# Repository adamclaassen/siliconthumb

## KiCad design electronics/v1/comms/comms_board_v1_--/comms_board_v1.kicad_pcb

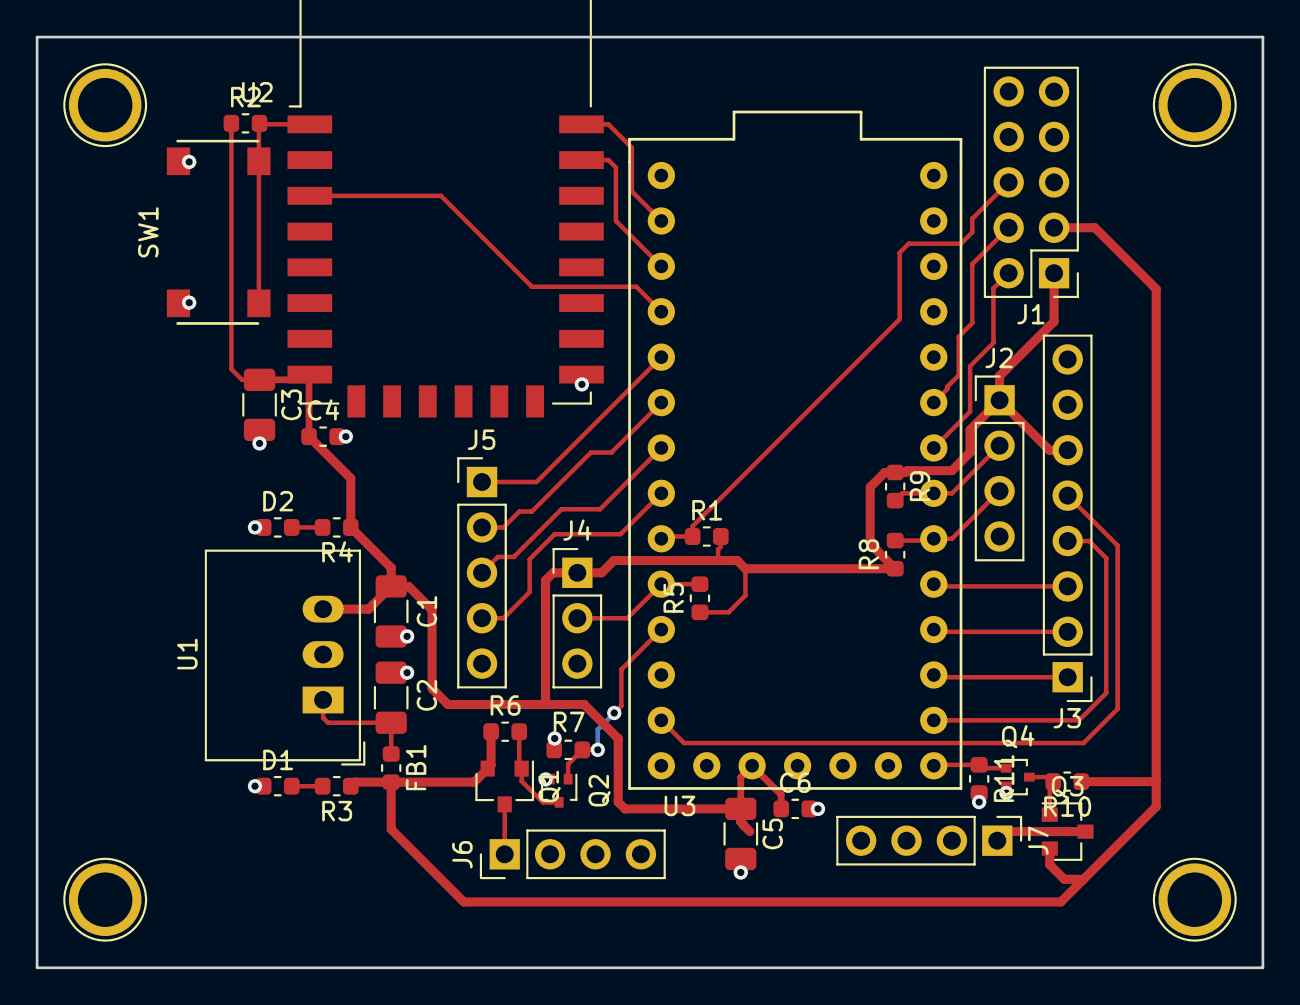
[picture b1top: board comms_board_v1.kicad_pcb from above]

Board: 2 copper layers, 68.6 x 52.1 mm, 35 parts (0 on the bottom side), 31 nets.

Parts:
C1, C2, C3, C5: 10uF; R_1206_3216Metric
C4, C6: 100nF; R_0603_1608Metric
D1, D2: LED; R_0603_1608Metric
FB1: Ferrite_Bead; R_0603_1608Metric
J1: Conn_02x05_Odd_Even; PinHeader_2x05_P2.54mm_Vertical
J2, J6, J7: Conn_01x04; PinHeader_1x04_P2.54mm_Vertical
J3: Conn_01x08; PinHeader_1x08_P2.54mm_Vertical
J4: Conn_01x03; PinHeader_1x03_P2.54mm_Vertical
J5: Conn_01x05; PinHeader_1x05_P2.54mm_Vertical
Q1, Q3: Q_PMOS_GSD; SOT-23
Q2, Q4: Q_NMOS_GSD; SOT-416
R1, R5: 4.7k; R_0603_1608Metric
R2: 100k; R_0603_1608Metric
R3: 22k; R_0603_1608Metric
R4: 2.2k; R_0603_1608Metric
R6, R7, R8, R9, R10, R11: 10k; R_0603_1608Metric
SW1: SW_Push; CnK_PTS645_SMD
U1: R-78E3.3-1.0; Converter_DCDC_RECOM_R-78E-0.5_THT
U2: ESP-12E
U3: TEENSY32; Teensy32

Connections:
+3.3V_MCU: C1.1, C3.1, C4.1, C5.1, C6.1, J1.1, J2.1, J3.6, J4.1, R1.2, R2.1, R4.1, R5.1, R8.1, R9.1, U1.3, U2.8, U3.32
+12V: FB1.2, J1.3, Q1.2, Q3.2, R3.1, R6.1, R10.1
/1WIRE_LED: J1.6, R1.1, U3.9
/1WIRE_SOIL: J4.2, R5.2, U3.10
/CS: J3.1, U3.17
/DISP_DC: J3.3, U3.19
/DISP_RST: J3.2, U3.18
/ESP_EN: U2.3, U3.4
/ESP_RX: U2.21, U3.3
/ESP_TX: U2.22, U3.2
/FAN: Q2.1, R7.1, U3.11
/IR_CTRL: J1.2, U3.22
/MOSI: J3.5, U3.13
/PUMP: Q4.1, R11.1, U3.15
/SCK: J3.4, U3.16
/SCL: J2.2, R9.2, U3.21
/SDA: J2.3, R8.2, U3.20
/UV_CTRL: J1.4, U3.23
GND: C1.2, C2.2, C3.2, C4.2, C5.2, C6.2, D1.1, D2.1, J1.5, J1.7, J1.8, J1.9, J1.10, J2.4, J3.8, J4.3, J5.5, J6.4, J7.4, Q2.2, Q4.2, R7.2, R11.2, SW1.1, U1.2, U2.15, U3.1, U3.27
unnamed: C2.1, FB1.1, U1.1
unnamed: D1.2, R3.2
unnamed: D2.2, R4.2
unnamed: J5.1, U3.5
unnamed: J5.2, U3.6
unnamed: J5.3, U3.7
unnamed: J5.4, U3.8
unnamed: J6.1, Q1.3
unnamed: J7.1, Q3.3
unnamed: Q1.1, Q2.3, R6.2
unnamed: Q3.1, Q4.3, R10.2
unnamed: R2.2, SW1.2, U2.1

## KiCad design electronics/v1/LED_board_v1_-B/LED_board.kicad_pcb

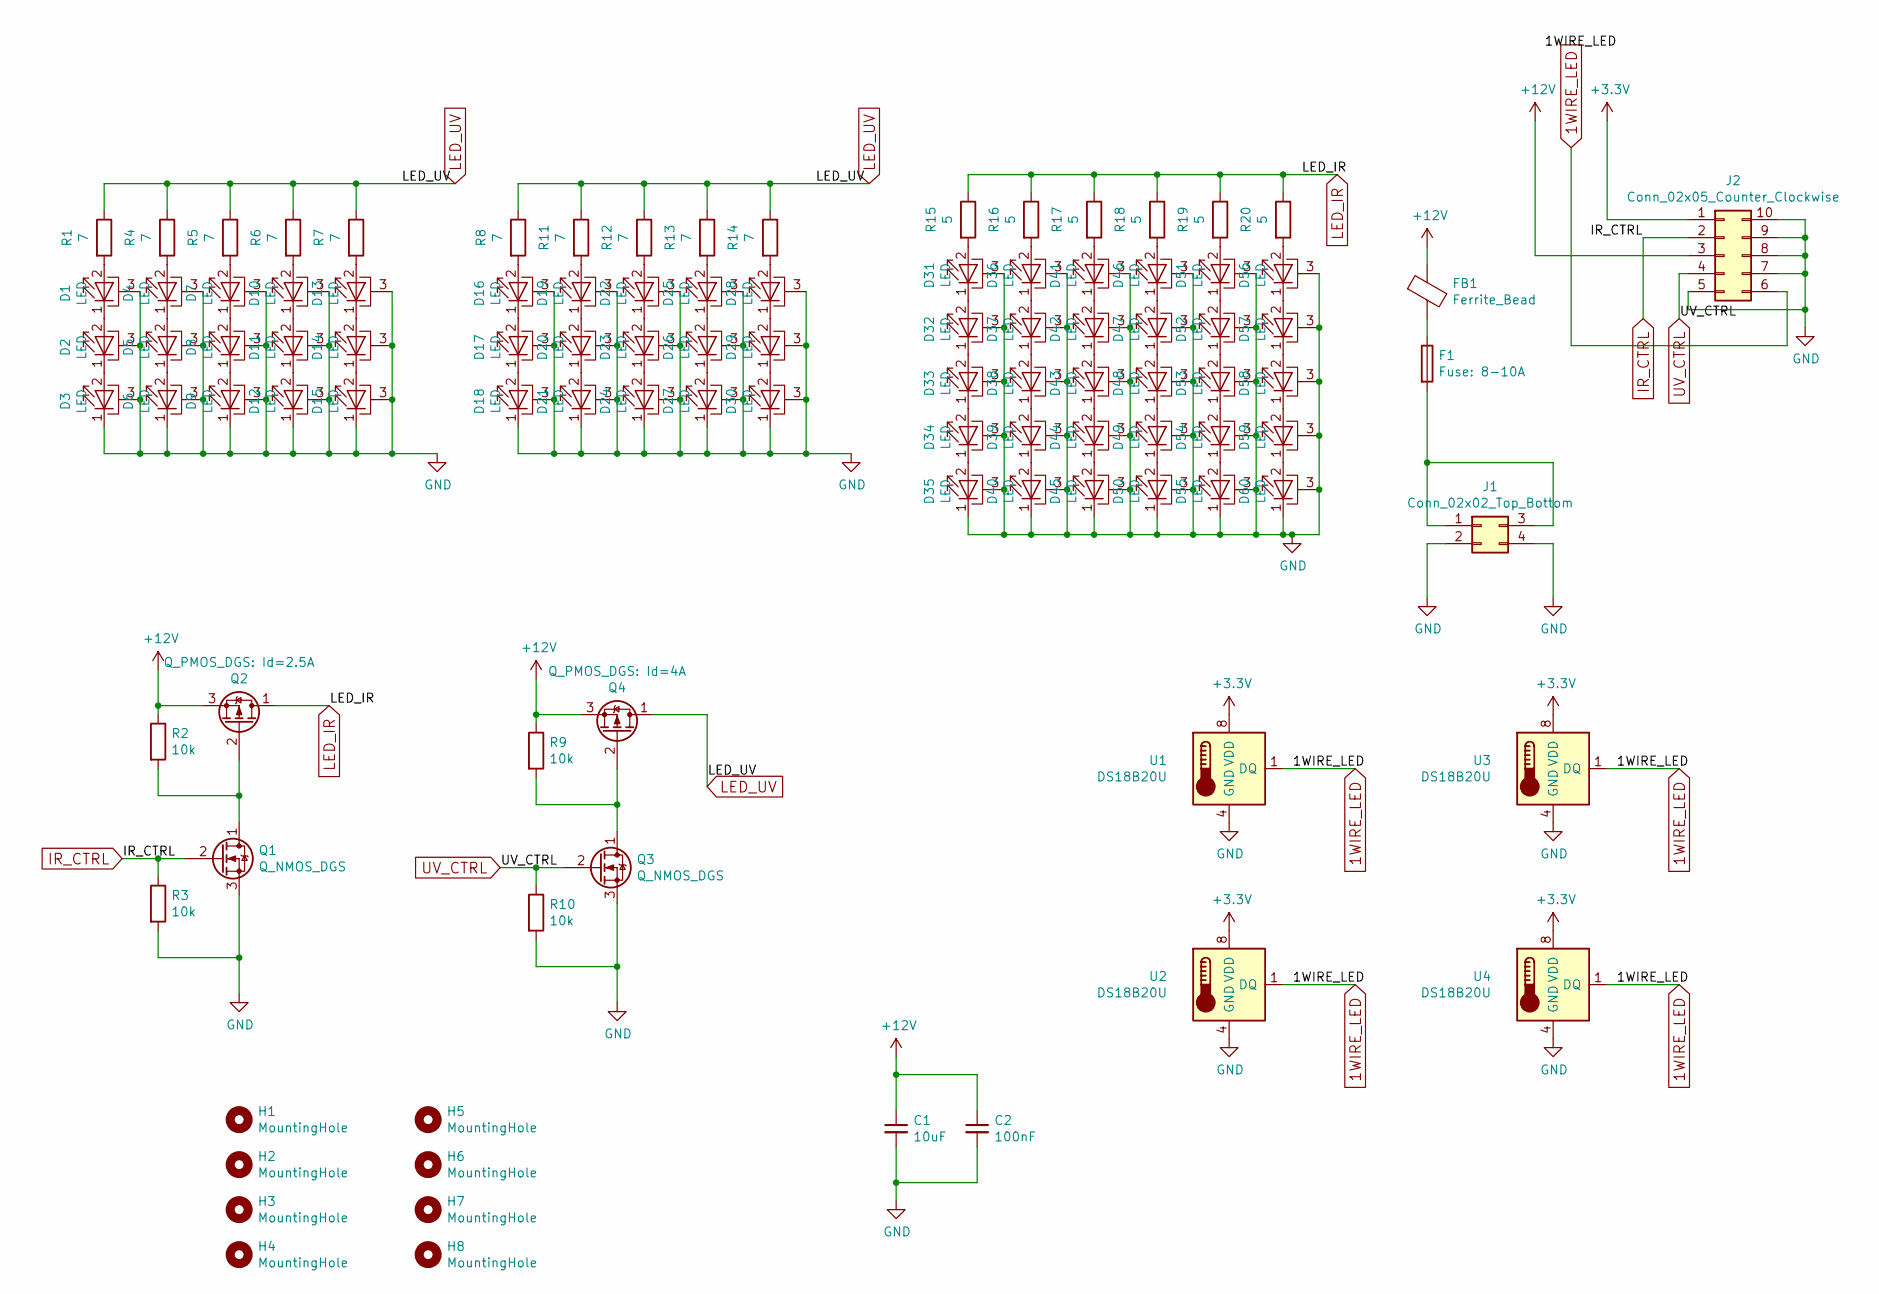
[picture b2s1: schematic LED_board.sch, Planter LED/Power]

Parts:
C1: 10uF; C_1206_3216Metric
C2: 100nF; C_0603_1608Metric
D1, D2, D3, D4, D5, D6, D7, D8, D9, D10, D11, D12, D13, D14, D15, D16, D17, D18, D19, D20, D21, D22, D23, D24, D25, D26, D27, D28, D29, D30, D31, D32, D33, D34, D35, D36, D37, D38, D39, D40, D41, D42, D43, D44, D45, D46, D47, D48, D49, D50, D51, D52, D53, D54, D55, D56, D57, D58, D59, D60: LED; LED_Cree-XP(EDIT)
F1: Fuse: 8-10A; Fuse_2512_6332Metric
FB1: Ferrite_Bead; L_2816_7142Metric
H1, H2, H3, H4, H5, H6, H7, H8: MountingHole; MountingHole_3.2mm_M3_ISO7380_Pad
J1: Conn_02x02_Top_Bottom; Molex_Micro-Fit_3.0_43045-0412_2x02_P3.00mm_Vertical
J2: Conn_02x05_Counter_Clockwise; PinHeader_2x05_P2.54mm_Vertical
Q1, Q3: Q_NMOS_DGS; SOT-416
Q2: Q_PMOS_DGS: Id=2.5A; SOT-23
Q4: Q_PMOS_DGS: Id=4A; SOT-23
R1, R4, R5, R6, R7, R8, R11, R12, R13, R14: 7; R_Axial_DIN0309_L9.0mm_D3.2mm_P12.70mm_Horizontal
R2, R3, R9, R10: 10k; R_0603_1608Metric
R15, R16, R17, R18, R19, R20: 5; R_Axial_DIN0309_L9.0mm_D3.2mm_P12.70mm_Horizontal
U1, U2, U3, U4: DS18B20U; MSOP-8-1EP_3x3mm_P0.65mm_EP2.54x2.8mm_ThermalVias

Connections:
1WIRE_LED: J2.6, U1.1 (DQ), U2.1 (DQ), U3.1 (DQ), U4.1 (DQ)
+3V3: J2.1, U1.8 (VDD), U2.8 (VDD), U3.8 (VDD), U4.8 (VDD)
+12V: C1.1, C2.1, FB1.1, J2.3, Q2.3 (S), Q4.3 (S), R2.1, R9.1
GND: C1.2, C2.2, D1.3 (PAD), D2.3 (PAD), D3.1 (K), D3.3 (PAD), D4.3 (PAD), D5.3 (PAD), D6.1 (K), D6.3 (PAD), D7.3 (PAD), D8.3 (PAD), D9.1 (K), D9.3 (PAD), D10.3 (PAD), D11.3 (PAD), D12.1 (K), D12.3 (PAD), D13.3 (PAD), D14.3 (PAD), D15.1 (K), D15.3 (PAD), D16.3 (PAD), D17.3 (PAD), D18.1 (K), D18.3 (PAD), D19.3 (PAD), D20.3 (PAD), D21.1 (K), D21.3 (PAD), D22.3 (PAD), D23.3 (PAD), D24.1 (K), D24.3 (PAD), D25.3 (PAD), D26.3 (PAD), D27.1 (K), D27.3 (PAD), D28.3 (PAD), D29.3 (PAD), D30.1 (K), D30.3 (PAD), D31.3 (PAD), D32.3 (PAD), D33.3 (PAD), D34.3 (PAD), D35.1 (K), D35.3 (PAD), D36.3 (PAD), D37.3 (PAD), D38.3 (PAD), D39.3 (PAD), D40.1 (K), D40.3 (PAD), D41.3 (PAD), D42.3 (PAD), D43.3 (PAD), D44.3 (PAD), D45.1 (K), D45.3 (PAD), D46.3 (PAD), D47.3 (PAD), D48.3 (PAD), D49.3 (PAD), D50.1 (K), D50.3 (PAD), D51.3 (PAD), D52.3 (PAD), D53.3 (PAD), D54.3 (PAD), D55.1 (K), D55.3 (PAD), D56.3 (PAD), D57.3 (PAD), D58.3 (PAD), D59.3 (PAD), D60.1 (K), D60.3 (PAD), J1.2, J1.4, J2.5, J2.7, J2.8, J2.9, J2.10, Q1.3 (S), Q3.3 (S), R3.2, R10.2, U1.4 (GND), U2.4 (GND), U3.4 (GND), U4.4 (GND)
IR_CTRL: J2.2, Q1.2 (G), R3.1
LED_IR: Q2.1 (D), R15.1, R16.1, R17.1, R18.1, R19.1, R20.1
LED_UV: Q4.1 (D), R1.1, R4.1, R5.1, R6.1, R7.1, R8.1, R11.1, R12.1, R13.1, R14.1
unnamed: D1.1 (K), D2.2 (A)
unnamed: D1.2 (A), R1.2
unnamed: D2.1 (K), D3.2 (A)
unnamed: D4.1 (K), D5.2 (A)
unnamed: D4.2 (A), R4.2
unnamed: D5.1 (K), D6.2 (A)
unnamed: D7.1 (K), D8.2 (A)
unnamed: D7.2 (A), R5.2
unnamed: D8.1 (K), D9.2 (A)
unnamed: D10.1 (K), D11.2 (A)
unnamed: D10.2 (A), R6.2
unnamed: D11.1 (K), D12.2 (A)
unnamed: D13.1 (K), D14.2 (A)
unnamed: D13.2 (A), R7.2
unnamed: D14.1 (K), D15.2 (A)
unnamed: D16.1 (K), D17.2 (A)
unnamed: D16.2 (A), R8.2
unnamed: D17.1 (K), D18.2 (A)
unnamed: D19.1 (K), D20.2 (A)
unnamed: D19.2 (A), R11.2
unnamed: D20.1 (K), D21.2 (A)
unnamed: D22.1 (K), D23.2 (A)
unnamed: D22.2 (A), R12.2
unnamed: D23.1 (K), D24.2 (A)
unnamed: D25.1 (K), D26.2 (A)
unnamed: D25.2 (A), R13.2
unnamed: D26.1 (K), D27.2 (A)
unnamed: D28.1 (K), D29.2 (A)
unnamed: D28.2 (A), R14.2
unnamed: D29.1 (K), D30.2 (A)
unnamed: D31.1 (K), D32.2 (A)
unnamed: D31.2 (A), R15.2
unnamed: D32.1 (K), D33.2 (A)
unnamed: D33.1 (K), D34.2 (A)
unnamed: D34.1 (K), D35.2 (A)
unnamed: D36.1 (K), D37.2 (A)
unnamed: D36.2 (A), R16.2
unnamed: D37.1 (K), D38.2 (A)
unnamed: D38.1 (K), D39.2 (A)
unnamed: D39.1 (K), D40.2 (A)
unnamed: D41.1 (K), D42.2 (A)
unnamed: D41.2 (A), R17.2
unnamed: D42.1 (K), D43.2 (A)
unnamed: D43.1 (K), D44.2 (A)
unnamed: D44.1 (K), D45.2 (A)
unnamed: D46.1 (K), D47.2 (A)
unnamed: D46.2 (A), R18.2
unnamed: D47.1 (K), D48.2 (A)
unnamed: D48.1 (K), D49.2 (A)
unnamed: D49.1 (K), D50.2 (A)
unnamed: D51.1 (K), D52.2 (A)
unnamed: D51.2 (A), R19.2
unnamed: D52.1 (K), D53.2 (A)
unnamed: D53.1 (K), D54.2 (A)
unnamed: D54.1 (K), D55.2 (A)
unnamed: D56.1 (K), D57.2 (A)
unnamed: D56.2 (A), R20.2
unnamed: D57.1 (K), D58.2 (A)
unnamed: D58.1 (K), D59.2 (A)
unnamed: D59.1 (K), D60.2 (A)
unnamed: F1.1, FB1.2
unnamed: F1.2, J1.1, J1.3
unnamed: Q1.1 (D), Q2.2 (G), R2.2
unnamed: Q3.1 (D), Q4.2 (G), R9.2
UV_CTRL: J2.4, Q3.2 (G), R10.1

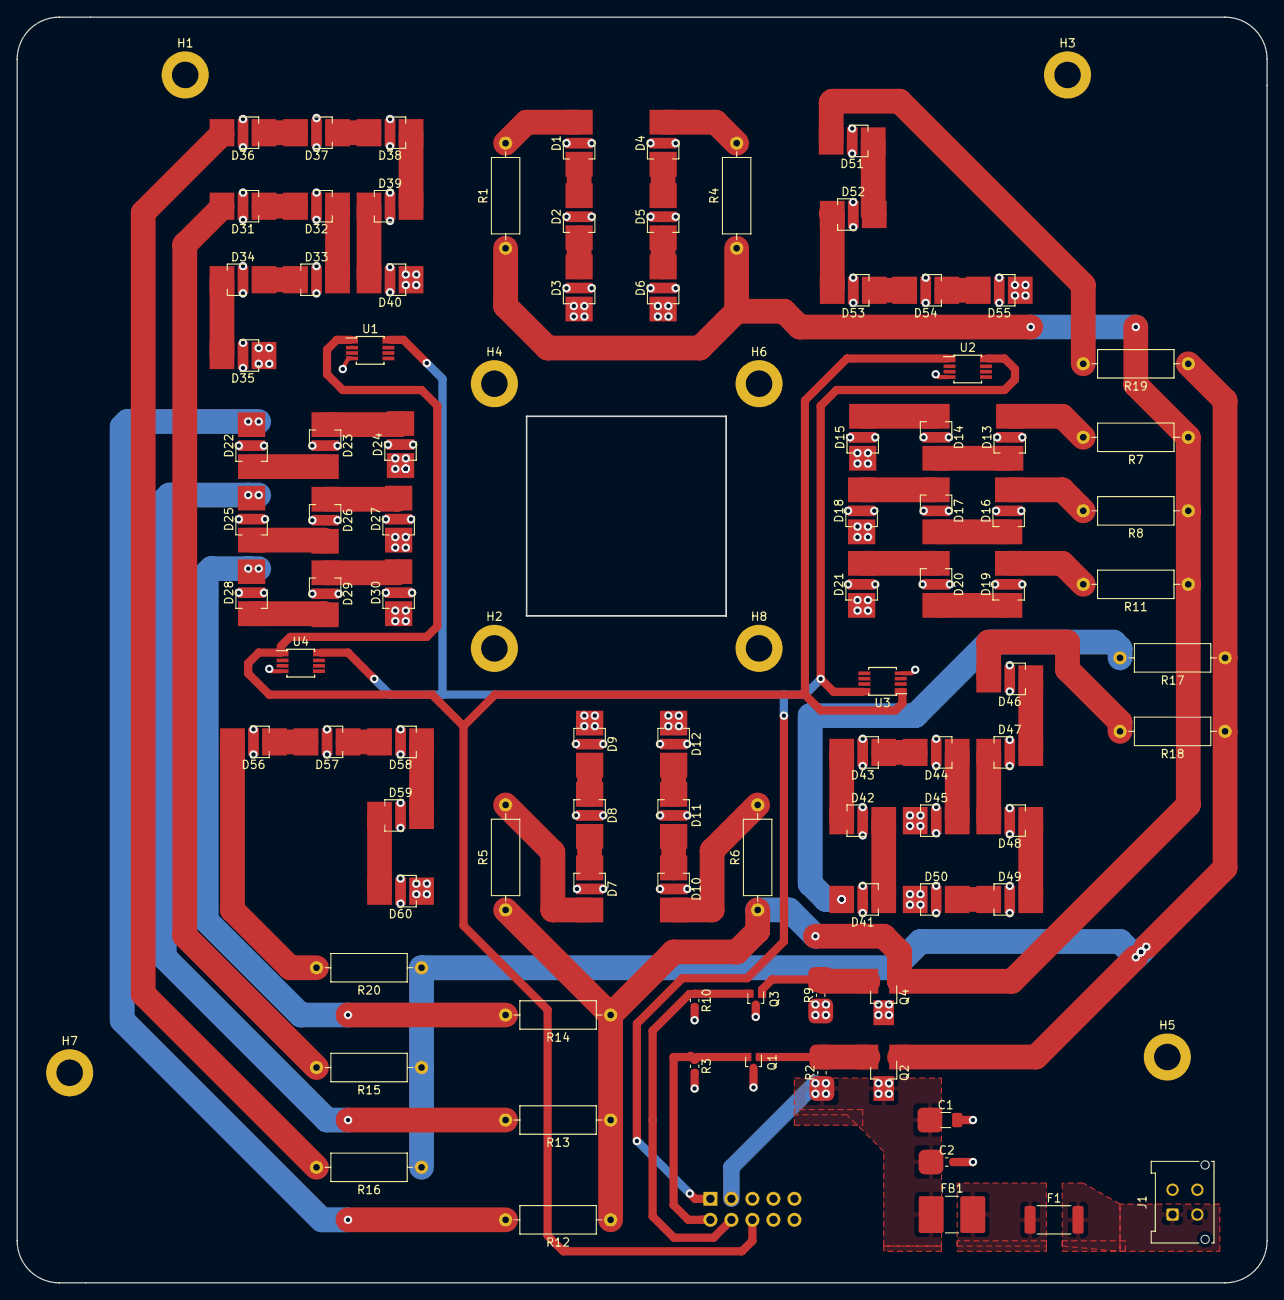
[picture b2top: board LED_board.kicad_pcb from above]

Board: 2 copper layers, 151.1 x 153.0 mm, 102 parts (1 on the bottom side), 72 nets.

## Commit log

2019-03-08 Initial commit, adding LED board to master
2019-03-20 Updated comms board files
2019-03-20 Updated LED package
2019-03-20 ACTUALLY updated LED footprints
2019-03-20 added correct footprint for D18B20U
2019-03-24 Fixed connector pinout
2019-03-24 Added pump header
2019-03-24 added control pin for pump
2019-03-24 reverting LED_board.kicad_pcb to 5d8140a
2019-03-24 Fixed LED board
2019-03-24 Added pump connector to comms board
2019-03-24 Changed a trace width
2019-04-02 Create ST_Code
2019-04-18 Generated STEP files
2019-05-02 Create ST_Code_V2
2019-05-07 Create SITHUMB_FINAL
2019-05-07 Create SI_TEST
2019-05-08 Create SISHOWCASE
